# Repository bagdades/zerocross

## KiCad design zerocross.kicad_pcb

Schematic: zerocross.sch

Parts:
C1: 220n/50V; C_0805_2012Metric
D1: MB6S; TO-269AA
D2: LL4148; D_MiniMELF
J1: OUTPUT; PinHeader_1x03_P2.54mm_Vertical
J2: INPUT; PinHeader_1x02_P2.54mm_Vertical
Q1, Q2: BC847; SOT-23
R1, R3: 330k; R_0805_2012Metric
R2: 270; R_0805_2012Metric
R4: 100k; R_0805_2012Metric
R5, R6: 120k; R_0805_2012Metric
R7: 2k; R_0805_2012Metric
R8: 10k; R_0805_2012Metric
U1: PC817; DIP-4_W7.62mm

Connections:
/+: D1.3 (+), R3.1, R5.2
unnamed: C1.1, D1.4 (-), Q1.2 (E), Q2.2 (E), R7.2
unnamed: C1.2, D2.1, R2.2, R4.1
unnamed: D1.1 (~~), J2.1
unnamed: D1.2 (~~), J2.2
unnamed: D2.2, R1.1
unnamed: J1.1, R8.1
unnamed: J1.2, R8.2, U1.4
unnamed: J1.3, U1.3
unnamed: Q1.1 (B), Q2.3 (C), R4.2
unnamed: Q1.3 (C), U1.2
unnamed: Q2.1 (B), R6.2, R7.1
unnamed: R1.2, R3.2
unnamed: R2.1, U1.1
unnamed: R5.1, R6.1

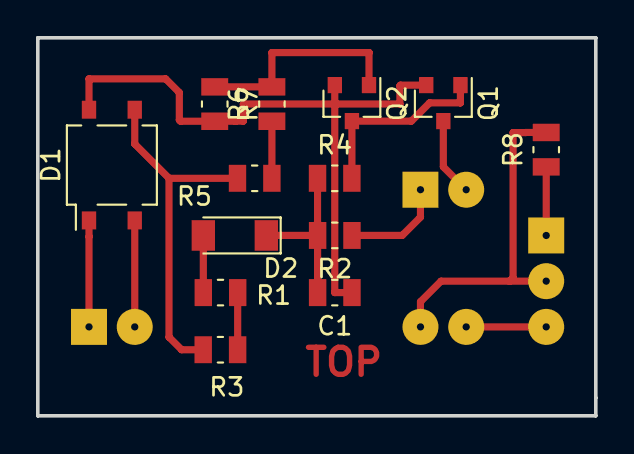
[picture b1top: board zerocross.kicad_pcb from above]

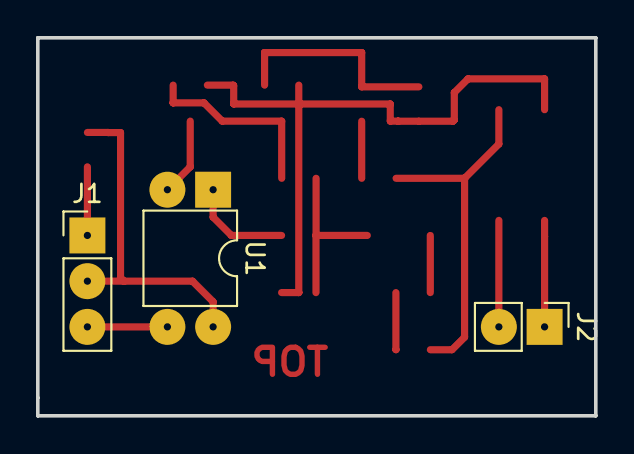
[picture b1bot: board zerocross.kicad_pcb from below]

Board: 2 copper layers, 31.0 x 21.0 mm, 16 parts (3 on the bottom side), 15 nets.

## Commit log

2018-03-06 Solder
